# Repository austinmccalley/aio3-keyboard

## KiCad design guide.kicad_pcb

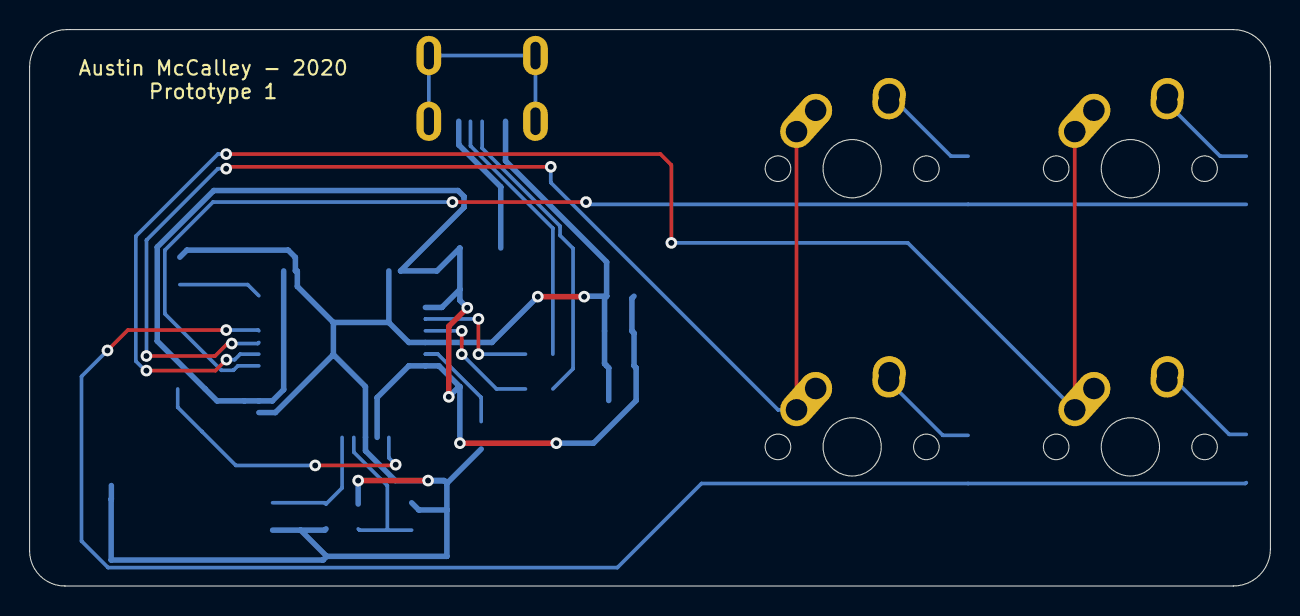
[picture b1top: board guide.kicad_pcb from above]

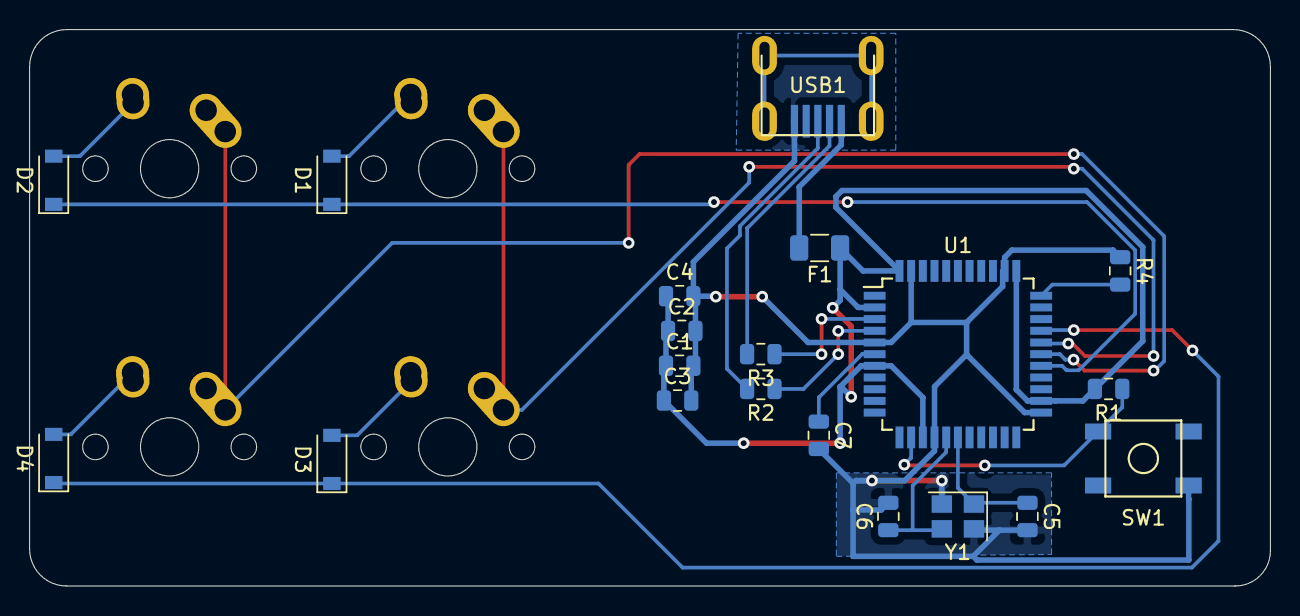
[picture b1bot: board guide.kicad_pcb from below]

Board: 2 copper layers, 85.0 x 38.1 mm, 24 parts (20 on the bottom side), 20 nets.

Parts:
C1, C2, C3: 0.1uF; C_0805_2012Metric
C4: 10uF; C_0805_2012Metric
C5, C6: 22pF; C_0805_2012Metric
C7: 1uF; C_0805_2012Metric
D1, D2, D3, D4: D_Small; D_SOD-123
F1: 500mA; Fuse_1206_3216Metric
MX1, MX2, MX3, MX4: MX-NoLED; MX-1U-NoLED
R1, R4: 10k; R_0805_2012Metric
R2, R3: 22; R_0805_2012Metric
SW1: SW_Push; SKQG-1155865
U1: ATmega32U4-AU; TQFP-44_10x10mm_P0.8mm
USB1: Molex-0548190589
Y1: Crystal_GND24_Small; Crystal_SMD_3225-4Pin_3.2x2.5mm

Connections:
+5V: C1.1, C2.1, C3.1, C4.1, F1.1, R1.2, U1.2, U1.7, U1.14, U1.24, U1.34, U1.44
COL0: MX1.1, MX3.1, U1.29
COL1: MX2.1, MX4.1, U1.28
D+: R2.2, USB1.3
D-: R3.2, USB1.4
GND: C1.2, C2.2, C3.2, C4.2, C5.2, C6.2, C7.2, R4.1, SW1.1, U1.5, U1.15, U1.23, U1.35, U1.43, USB1.1, Y1.2, Y1.4
unnamed: C5.1, U1.17, Y1.1
unnamed: C6.1, U1.16, Y1.3
unnamed: C7.1, U1.6
unnamed: D1.2, MX1.2
unnamed: D2.2, MX2.2
unnamed: D3.2, MX3.2
unnamed: D4.2, MX4.2
unnamed: R1.1, SW1.2, U1.13
unnamed: R2.1, U1.4
unnamed: R3.1, U1.3
unnamed: R4.2, U1.33
ROW0: D1.1, D2.1, U1.27
ROW1: D3.1, D4.1, U1.30
VCC: F1.2, USB1.5

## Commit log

2020-07-09 Added submodules
2020-07-09 Added libs
2020-07-09 Schematic done for 2x2
2020-07-09 Done?
2020-07-09 Done??
